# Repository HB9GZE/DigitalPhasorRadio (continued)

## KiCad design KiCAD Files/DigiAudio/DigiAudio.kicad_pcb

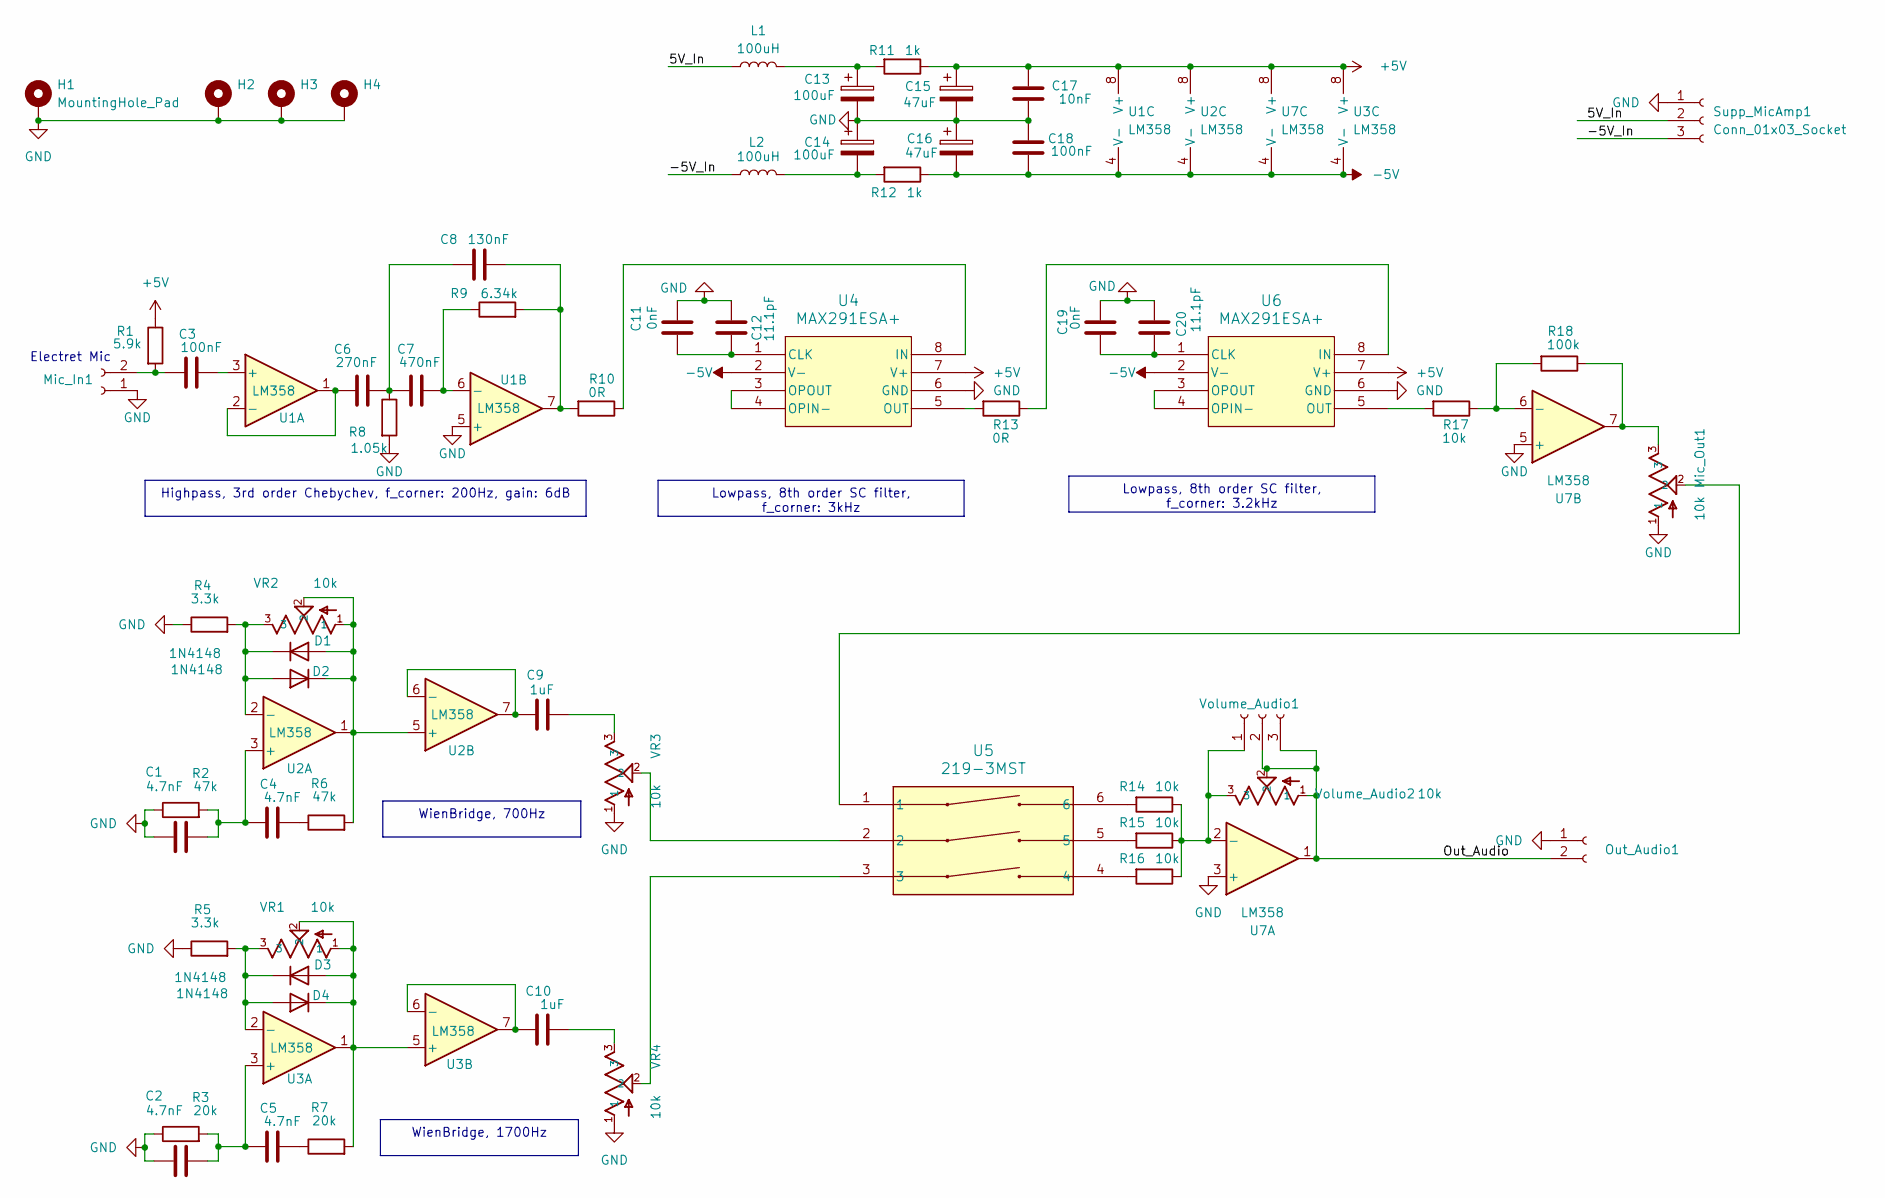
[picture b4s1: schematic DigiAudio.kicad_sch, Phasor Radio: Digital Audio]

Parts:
C1, C2, C4, C5: 4.7nF; C_0805_2012Metric_Pad1.18x1.45mm_HandSolder
C3, C18: 100nF; C_0805_2012Metric_Pad1.18x1.45mm_HandSolder
C6: 270nF; C_0805_2012Metric_Pad1.18x1.45mm_HandSolder
C7: 470nF; C_0805_2012Metric_Pad1.18x1.45mm_HandSolder
C8: 130nF; C_0805_2012Metric_Pad1.18x1.45mm_HandSolder
C9, C10: 1uF; C_0805_2012Metric_Pad1.18x1.45mm_HandSolder
C11, C19: 0nF; C_0805_2012Metric_Pad1.18x1.45mm_HandSolder
C12, C20: 11.1pF; C_0805_2012Metric_Pad1.18x1.45mm_HandSolder
C13, C14: 100uF; CP_EIA-3216-12_Kemet-S_Pad1.58x1.35mm_HandSolder
C15, C16: 47uF; CP_EIA-3216-12_Kemet-S_Pad1.58x1.35mm_HandSolder
C17: 10nF; C_0805_2012Metric_Pad1.18x1.45mm_HandSolder
D1, D2, D3, D4: 1N4148; D_SOD-123
H1, H2, H3, H4: MountingHole_Pad; MountingHole_2.5mm_Pad_TopBottom
L1, L2: 100uH; L_0805_2012Metric_Pad1.15x1.40mm_HandSolder
Mic_In1: Conn_01x02_Socket; JST_EH_B2B-EH-A_1x02_P2.50mm_Vertical
Mic_Out1: 10k; TRIM_35WR10KLFTR
Out_Audio1: Conn_01x02_Socket; JST_EH_B2B-EH-A_1x02_P2.50mm_Vertical
R1: 5.9k; R_0805_2012Metric_Pad1.20x1.40mm_HandSolder
R2, R6: 47k; R_0805_2012Metric_Pad1.20x1.40mm_HandSolder
R3, R7: 20k; R_0805_2012Metric_Pad1.20x1.40mm_HandSolder
R4, R5: 3.3k; R_0805_2012Metric_Pad1.20x1.40mm_HandSolder
R8: 1.05k; R_0805_2012Metric_Pad1.20x1.40mm_HandSolder
R9: 6.34k; R_0805_2012Metric_Pad1.20x1.40mm_HandSolder
R10, R13: 0R; R_0805_2012Metric_Pad1.20x1.40mm_HandSolder
R11, R12: 1k; R_0805_2012Metric_Pad1.20x1.40mm_HandSolder
R14, R15, R16, R17: 10k; R_0805_2012Metric_Pad1.20x1.40mm_HandSolder
R18: 100k; R_0805_2012Metric_Pad1.20x1.40mm_HandSolder
Supp_MicAmp1: Conn_01x03_Socket; JST_EH_B3B-EH-A_1x03_P2.50mm_Vertical
U1, U2, U3, U7: LM358; SOIC-8_3.9x4.9mm_P1.27mm
U4, U6: MAX291ESA+; MAX291
U5: 219-3MST; SW3_219-3MST_CTS
VR1, VR2, VR3, VR4: 10k; TRIM_35WR10KLFTR
Volume_Audio1: Conn_01x03_Socket; JST_EH_B3B-EH-A_1x03_P2.50mm_Vertical
Volume_Audio2: 10k; TRIM_35WR10KLFTR

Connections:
+5V: C15.1, C17.2, R1.1, R11.1, U1.8 (V+), U2.8 (V+), U3.8 (V+), U4.7 (V+), U6.7 (V+), U7.8 (V+)
-5V: C16.2, C18.1, R12.1, U1.4 (V-), U2.4 (V-), U3.4 (V-), U4.2 (V-), U6.2 (V-), U7.4 (V-)
/5V_In: L1.1, Supp_MicAmp1.2
/-5V_In: L2.1, Supp_MicAmp1.3
/Out_Audio: Out_Audio1.2, U7.1, Volume_Audio1.2, Volume_Audio1.3, Volume_Audio2.1, Volume_Audio2.2; also elsewhere on the board
GND: C1.1, C2.1, C11.2, C12.2, C13.2, C14.1, C15.2, C16.1, C17.1, C18.2, C19.2, C20.2, H1.1, H2.1, H3.1, H4.1, Mic_In1.1, Mic_Out1.1, Out_Audio1.1, R2.1, R3.1, R4.1, R5.1, R8.2, Supp_MicAmp1.1, U1.5 (+), U4.6 (GND), U6.6 (GND), U7.3 (+), U7.5 (+), VR3.1, VR4.1; also elsewhere on the board
unnamed: C4.2, R6.1
unnamed: C5.2, R7.1
unnamed: C6.2, C7.1, C8.1, R8.1
unnamed: C8.2, R9.2, R10.2, U1.7
unnamed: C9.2, VR3.3
unnamed: C10.2, VR4.3
unnamed: C13.1, L1.2, R11.2
unnamed: C14.2, L2.2, R12.2
unnamed: D1.2 (A), D2.1 (K), R6.2, U2.1, U2.5 (+), VR2.1, VR2.2
unnamed: D1.1 (K), D2.2 (A), R4.2, U2.2 (-), VR2.3
unnamed: D3.2 (A), D4.1 (K), R7.2, U3.1, U3.5 (+), VR1.1, VR1.2
unnamed: D3.1 (K), D4.2 (A), R5.2, U3.2 (-), VR1.3
unnamed 18: C3.1, Mic_In1.2, R1.2; also elsewhere on the board
unnamed 19: Mic_Out1.2, U5.1; also elsewhere on the board
unnamed 20: Mic_Out1.3, R18.1, U7.7; also elsewhere on the board
unnamed: R14.2, U5.6
unnamed: R15.2, U5.5
unnamed: R16.2, U5.4
unnamed: C3.2, U1.3 (+)
unnamed: C6.1, U1.1, U1.2 (-)
unnamed: C7.2, R9.1, U1.6 (-)
unnamed: C1.2, C4.1, R2.2, U2.3 (+)
unnamed: C9.1, U2.6 (-), U2.7
unnamed: C2.2, C5.1, R3.2, U3.3 (+)
unnamed: C10.1, U3.6 (-), U3.7
unnamed: C11.1, C12.1, U4.1 (CLK)
unnamed: R10.1, U4.8 (IN)
unnamed: U4.3 (OPOUT), U4.4 (OPIN-)
unnamed: R13.2, U4.5 (OUT)
unnamed: U5.2, VR3.2
unnamed: U5.3, VR4.2
unnamed: C19.1, C20.1, U6.1 (CLK)
unnamed: R13.1, U6.8 (IN)
unnamed: U6.3 (OPOUT), U6.4 (OPIN-)
unnamed: R17.2, U6.5 (OUT)
unnamed 41: R14.1, R15.1, R16.1, U7.2 (-), Volume_Audio1.1, Volume_Audio2.3; also elsewhere on the board
unnamed: R17.1, R18.2, U7.6 (-)

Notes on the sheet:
Lowpass, 8th order SC filter, f_corner: 3kHz
WienBridge, 1700Hz
Highpass, 3rd order Chebychev, f_corner: 200Hz, gain: 6dB
WienBridge, 700Hz
Lowpass, 8th order SC filter, f_corner: 3.2kHz
Electret Mic

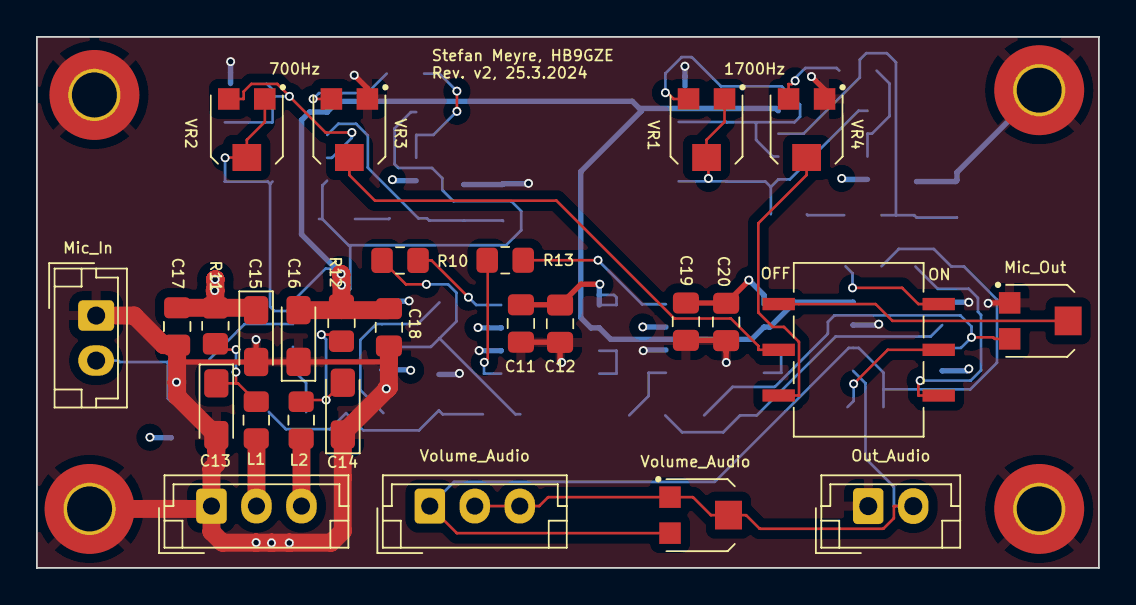
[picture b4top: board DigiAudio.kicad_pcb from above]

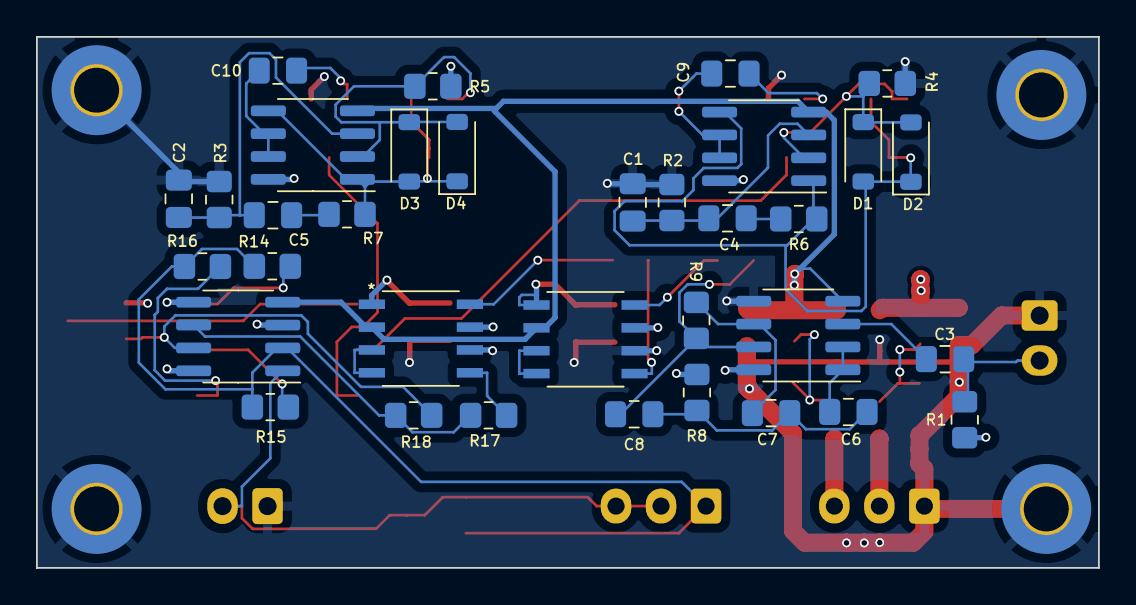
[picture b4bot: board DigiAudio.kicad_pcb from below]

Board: 4 copper layers, 59.0 x 29.5 mm, 65 parts (34 on the bottom side), 43 nets.

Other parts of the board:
Mic_In: Conn_01x02_Socket; JST_EH_B2B-EH-A_1x02_P2.50mm_Vertical
Mic_Out: 10k; TRIM_35WR10KLFTR
Out_Audio: Conn_01x02_Socket; JST_EH_B2B-EH-A_1x02_P2.50mm_Vertical
Volume_Audio: 10k; TRIM_35WR10KLFTR
Volume_Audio#2: Conn_01x03_Socket; JST_EH_B3B-EH-A_1x03_P2.50mm_Vertical

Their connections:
/Out_Audio: Out_Audio.2, Volume_Audio.1, Volume_Audio.2, Volume_Audio#2.2, Volume_Audio#2.3; also elsewhere on the board
GND: Mic_In.1, Mic_Out.1, Out_Audio.1; also elsewhere on the board
unnamed 18: Mic_In.2; also elsewhere on the board
unnamed 19: Mic_Out.2; also elsewhere on the board
unnamed 20: Mic_Out.3; also elsewhere on the board
unnamed 41: Volume_Audio.3, Volume_Audio#2.1; also elsewhere on the board

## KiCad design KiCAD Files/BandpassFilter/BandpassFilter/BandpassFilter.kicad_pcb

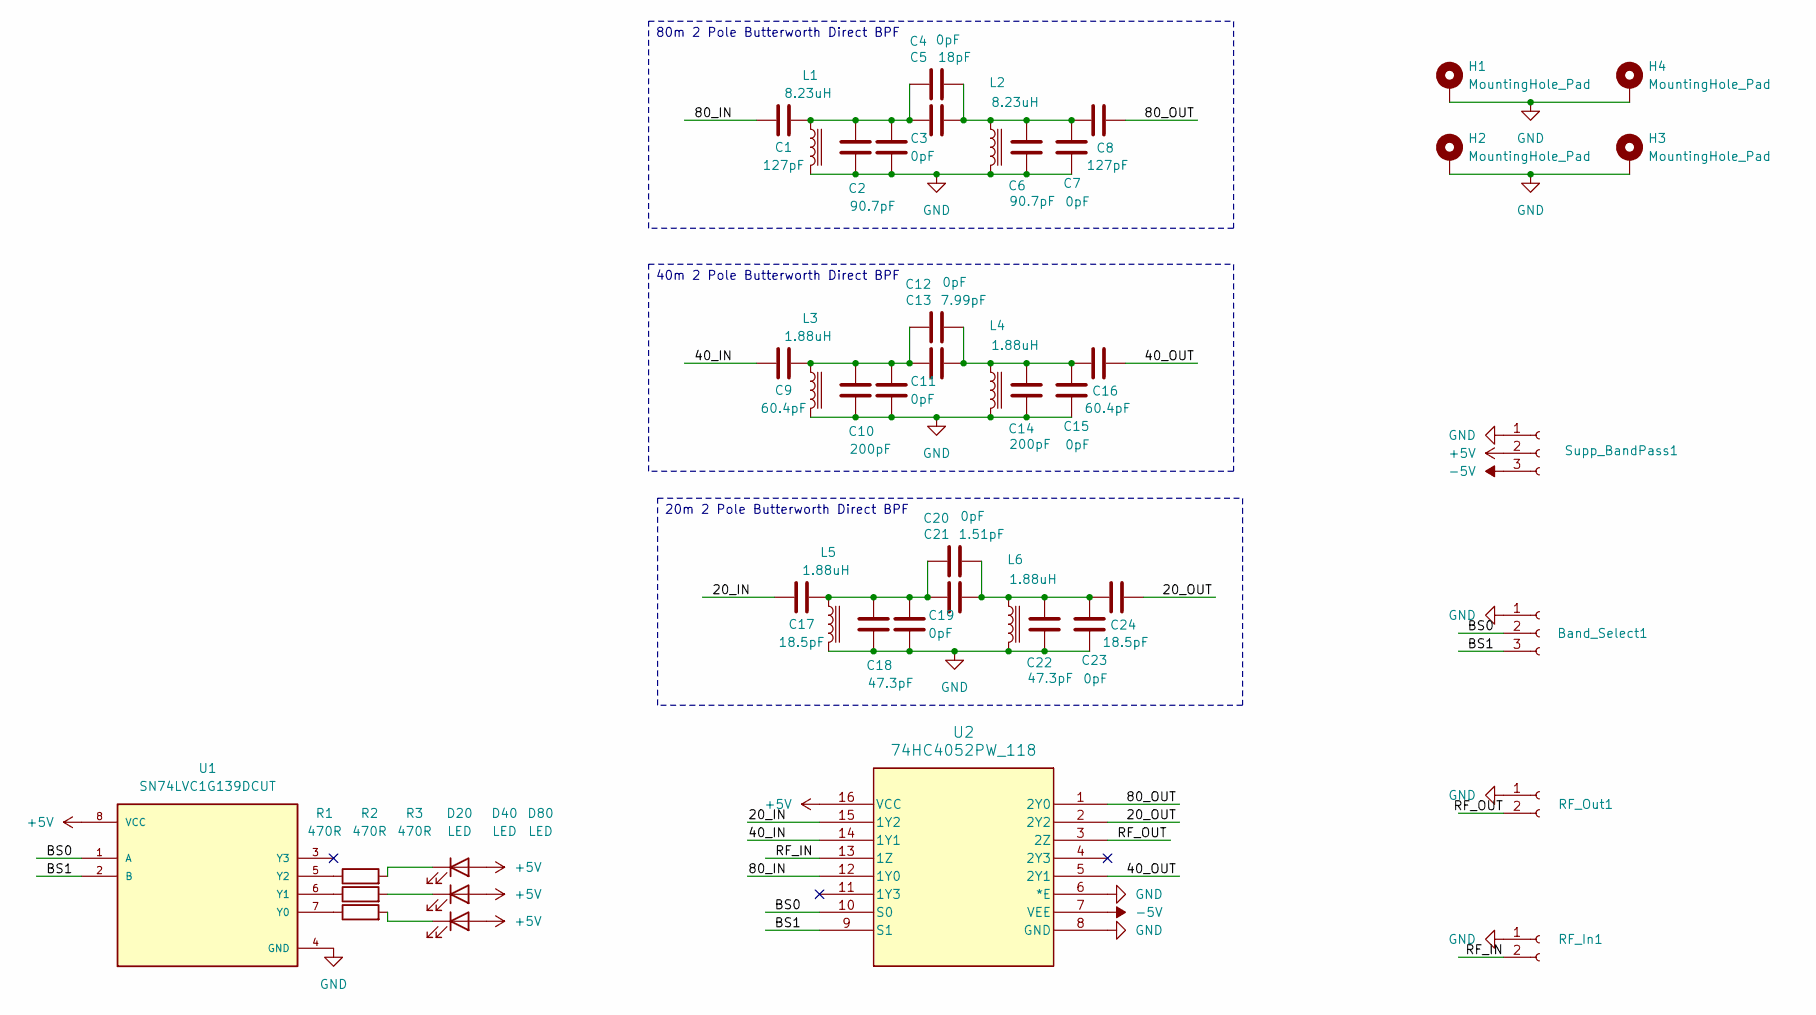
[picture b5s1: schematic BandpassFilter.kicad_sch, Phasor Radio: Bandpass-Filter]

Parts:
Band_Select1: JST_EH_B3B-EH-A_1x03_P2.50mm_Vertical
C1, C8: 127pF; C_0805_2012Metric_Pad1.18x1.45mm_HandSolder
C2, C6: 90.7pF; C_0805_2012Metric_Pad1.18x1.45mm_HandSolder
C3, C4, C7, C11, C12, C15, C19, C20, C23: 0pF; C_0805_2012Metric_Pad1.18x1.45mm_HandSolder
C5: 18pF; C_0805_2012Metric_Pad1.18x1.45mm_HandSolder
C9, C16: 60.4pF; C_0805_2012Metric_Pad1.18x1.45mm_HandSolder
C10, C14: 200pF; C_0805_2012Metric_Pad1.18x1.45mm_HandSolder
C13: 7.99pF; C_0805_2012Metric_Pad1.18x1.45mm_HandSolder
C17, C24: 18.5pF; C_0805_2012Metric_Pad1.18x1.45mm_HandSolder
C18, C22: 47.3pF; C_0805_2012Metric_Pad1.18x1.45mm_HandSolder
C21: 1.51pF; C_0805_2012Metric_Pad1.18x1.45mm_HandSolder
D20, D40, D80: LED; LED_0805_2012Metric_Pad1.15x1.40mm_HandSolder
H1, H2, H3, H4: MountingHole_Pad; MountingHole_2.5mm_Pad_TopBottom
L1, L2: 8.23uH; L_Toroid_Vertical_L19.1mm_W8.1mm_P7.10mm_Bourns_5700
L3, L4, L5, L6: 1.88uH; L_Toroid_Vertical_L19.1mm_W8.1mm_P7.10mm_Bourns_5700
R1, R2, R3: 470R; R_0805_2012Metric_Pad1.20x1.40mm_HandSolder
RF_In1: PinHeader_1x02_P2.54mm_Vertical
RF_Out1: PinHeader_1x02_P2.54mm_Vertical
Supp_BandPass1: JST_EH_B3B-EH-A_1x03_P2.50mm_Vertical
U1: SN74LVC1G139DCUT; SOP50P310X90-8N; PARTREV E
U2: 74HC4052PW_118; TSSOP16_5P1X4P5_NEX

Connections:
+5V: D20.2 (A), D40.2 (A), D80.2 (A), Supp_BandPass1.2, U1.8 (VCC), U2.16 (VCC); also elsewhere on the board
-5V: Supp_BandPass1.3, U2.7 (VEE); also elsewhere on the board
/20_IN: C17.1, U2.15 (1Y2)
/20_OUT: C24.2, U2.2 (2Y2)
/40_IN: C9.1, U2.14 (1Y1)
/40_OUT: C16.2, U2.5 (2Y1)
/80_IN: C1.1, U2.12 (1Y0)
/80_OUT: C8.2, U2.1 (2Y0)
/BS0: Band_Select1.2, U1.1 (A), U2.10 (S0); also elsewhere on the board
/BS1: Band_Select1.3, U1.2 (B), U2.9 (S1); also elsewhere on the board
/RF_IN: RF_In1.2, U2.13 (1Z); also elsewhere on the board
/RF_OUT: RF_Out1.2, U2.3 (2Z); also elsewhere on the board
GND: Band_Select1.1, C2.1, C3.1, C6.1, C7.1, C10.1, C11.1, C14.1, C15.1, C18.1, C19.1, C22.1, C23.1, H1.1, H2.1, H3.1, H4.1, L1.2, L2.2, L3.2, L4.2, L5.2, L6.2, RF_In1.1, RF_Out1.1, Supp_BandPass1.1, U1.4 (GND), U2.6 (*E), U2.8 (GND); also elsewhere on the board
unnamed: C1.2, C2.2, C3.2, C4.2, C5.2, L1.1
unnamed: C4.1, C5.1, C6.2, C7.2, C8.1, L2.1
unnamed: C9.2, C10.2, C11.2, C12.2, C13.2, L3.1
unnamed: C12.1, C13.1, C14.2, C15.2, C16.1, L4.1
unnamed: C17.2, C18.2, C19.2, C20.2, C21.2, L5.1
unnamed: C20.1, C21.1, C22.2, C23.2, C24.1, L6.1
unnamed: D20.1 (K), R1.2
unnamed: D40.1 (K), R2.2
unnamed: D80.1 (K), R3.2
unnamed: R3.1, U1.7 (Y0)
unnamed: R2.1, U1.6 (Y1)
unnamed: R1.1, U1.5 (Y2)

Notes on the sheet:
40m 2 Pole Butterworth Direct BPF
20m 2 Pole Butterworth Direct BPF
80m 2 Pole Butterworth Direct BPF

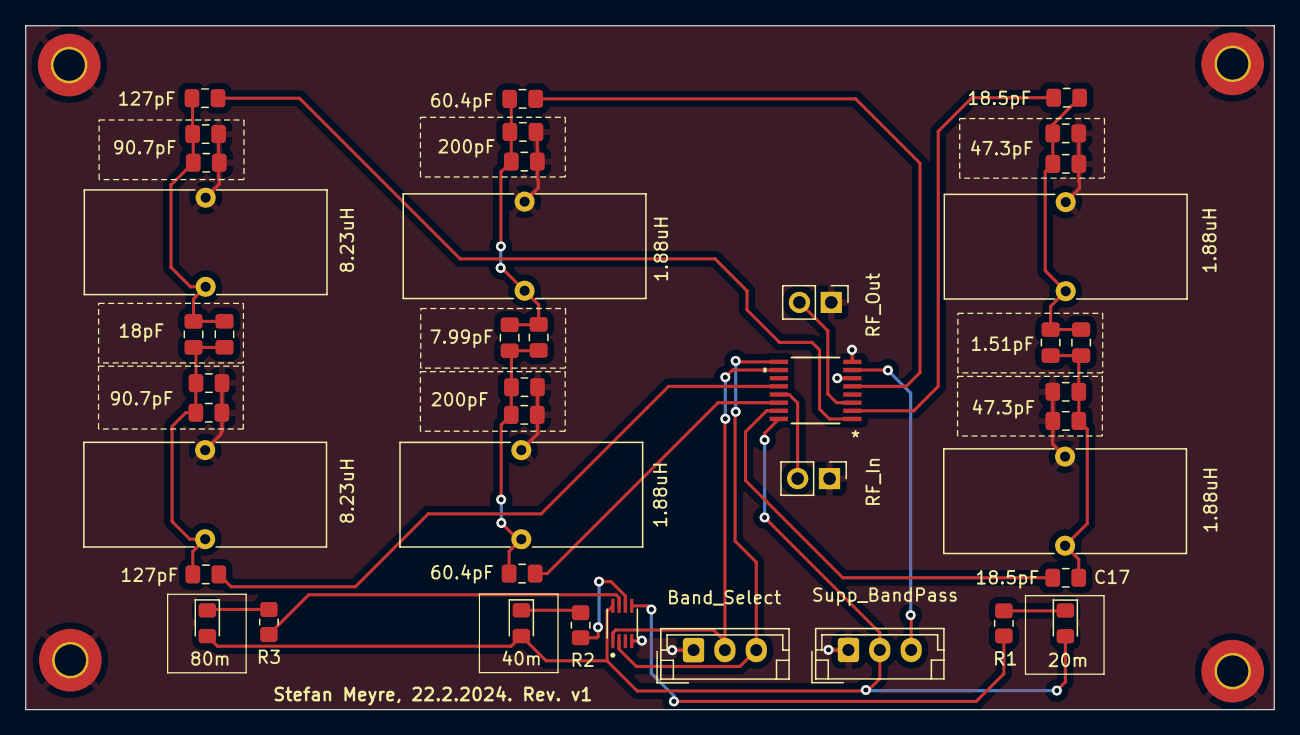
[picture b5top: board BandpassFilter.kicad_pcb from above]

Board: 2 copper layers, 99.5 x 54.5 mm, 46 parts (0 on the bottom side), 25 nets.

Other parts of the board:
Band_Select: JST_EH_B3B-EH-A_1x03_P2.50mm_Vertical
RF_In: PinHeader_1x02_P2.54mm_Vertical
RF_Out: PinHeader_1x02_P2.54mm_Vertical
Supp_BandPass: JST_EH_B3B-EH-A_1x03_P2.50mm_Vertical

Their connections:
+5V: Supp_BandPass.2; also elsewhere on the board
-5V: Supp_BandPass.3; also elsewhere on the board
/BS0: Band_Select.2; also elsewhere on the board
/BS1: Band_Select.3; also elsewhere on the board
/RF_IN: RF_In.2; also elsewhere on the board
/RF_OUT: RF_Out.2; also elsewhere on the board
GND: Band_Select.1, RF_In.1, RF_Out.1, Supp_BandPass.1; also elsewhere on the board

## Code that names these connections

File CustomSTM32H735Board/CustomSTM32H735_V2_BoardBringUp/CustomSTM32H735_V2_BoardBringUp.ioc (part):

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Mcu.Name=STM32H735IGKx
Mcu.Package=UFBGA176
Mcu.UserName=STM32H735IGKx
PA0.GPIOParameters=GPIO_Speed,GPIO_Label
PA0.GPIO_Label=VSYNC_FREQ
PA0.GPIO_Speed=GPIO_SPEED_FREQ_VERY_HIGH
PA0.Signal=GPIO_Output
PA0_C.Signal=ADCx_INP0
PA12.GPIOParameters=GPIO_Label
PA12.GPIO_Label=LSBUSB
PA12.Signal=GPIO_Output
PA13(JTMS/SWDIO).Mode=Serial_Wire
PA13(JTMS/SWDIO).Signal=DEBUG_JTMS-SWDIO
PA14(JTCK/SWCLK).Mode=Serial_Wire
PA14(JTCK/SWCLK).Signal=DEBUG_JTCK-SWCLK
PA15(JTDI).Signal=S_TIM2_CH1_ETR
PA1_C.Signal=ADCx_INP1
PA3.GPIOParameters=GPIO_Speed
PA3.GPIO_Speed=GPIO_SPEED_FREQ_VERY_HIGH
PA3.Mode=RGB888
PA3.Signal=LTDC_B5
PA4.GPIOParameters=GPIO_Speed
PA4.GPIO_Speed=GPIO_SPEED_FREQ_VERY_HIGH
PA4.Mode=RGB888
PA4.Signal=LTDC_VSYNC
PA5.Signal=COMP_DAC12_group
PA6.GPIOParameters=GPIO_Speed
PA6.GPIO_Speed=GPIO_SPEED_FREQ_VERY_HIGH
PA6.Mode=RGB888
PA6.Signal=LTDC_G2
PA8.GPIOParameters=GPIO_Speed
PA8.GPIO_Speed=GPIO_SPEED_FREQ_VERY_HIGH
PA8.Mode=RGB888
PA8.Signal=LTDC_B3
PB0.GPIOParameters=GPIO_Speed
PB0.GPIO_Speed=GPIO_SPEED_FREQ_VERY_HIGH
PB0.Mode=RGB888
PB0.Signal=LTDC_G1
PB1.GPIOParameters=GPIO_Speed
PB1.GPIO_Speed=GPIO_SPEED_FREQ_VERY_HIGH
PB1.Mode=RGB888
PB1.Signal=LTDC_G0
PB10.Mode=I2C
PB10.Signal=I2C2_SCL
PB11.Mode=I2C
PB11.Signal=I2C2_SDA
PB12.GPIOParameters=GPIO_Label
PB12.GPIO_Label=S0
PB12.Signal=GPIO_Output
PB13.GPIOParameters=GPIO_Label
PB13.GPIO_Label=S1
PB13.Signal=GPIO_Output
PB14.GPIOParameters=GPIO_Speed,GPIO_Label
PB14.GPIO_Label=FRAME_RATE
PB14.GPIO_Speed=GPIO_SPEED_FREQ_VERY_HIGH
PB14.Signal=GPIO_Output
PB15.GPIOParameters=GPIO_Speed,GPIO_Label
PB15.GPIO_Label=MCU_ACTIVE
PB15.GPIO_Speed=GPIO_SPEED_FREQ_VERY_HIGH
PB15.Signal=GPIO_Output
PB2.Mode=OCTOSPI1_Port1_DQS
PB2.Signal=OCTOSPIM_P1_DQS
PB3(JTDO/TRACESWO).Signal=S_TIM2_CH2
PB8.GPIOParameters=GPIO_Speed
PB8.GPIO_Speed=GPIO_SPEED_FREQ_VERY_HIGH
PB8.Mode=RGB888
PB8.Signal=LTDC_B6
PB9.GPIOParameters=GPIO_Speed
PB9.GPIO_Speed=GPIO_SPEED_FREQ_VERY_HIGH
PB9.Mode=RGB888
PB9.Signal=LTDC_B7
PC13.GPIOParameters=GPIO_Label
PC13.GPIO_Label=GPIO_PC13
PC13.Signal=GPIO_Output
PC2_C.Mode=IN0-Single-Ended
PC2_C.Signal=ADC3_INP0
PC4.Mode=Follower-DAC_OUT1-INP
PC4.Signal=OPAMP1_VOUT
PC6.GPIOParameters=GPIO_Speed
PC6.GPIO_Speed=GPIO_SPEED_FREQ_VERY_HIGH
PC6.Mode=RGB888
PC6.Signal=LTDC_HSYNC
PC7.GPIOParameters=GPIO_Speed
PC7.GPIO_Speed=GPIO_SPEED_FREQ_VERY_HIGH
PC7.Mode=RGB888
PC7.Signal=LTDC_G6
PC9.Mode=I2C
PC9.Signal=I2C3_SDA
PD0.GPIOParameters=GPIO_Speed
PD0.GPIO_Speed=GPIO_SPEED_FREQ_VERY_HIGH
PD0.Mode=RGB888
PD0.Signal=LTDC_B1
PD1.Mode=Asynchronous
PD1.Signal=UART4_TX
PD10.GPIOParameters=GPIO_Speed,PinState,GPIO_PuPd,GPIO_Label
PD10.GPIO_Label=LCD_DISP
PD10.GPIO_PuPd=GPIO_NOPULL
PD10.GPIO_Speed=GPIO_SPEED_FREQ_LOW
PD10.PinState=GPIO_PIN_RESET
PD10.Signal=GPIO_Output
PD11.Mode=OCTOSPI1_IOL_Port1L
PD11.Signal=OCTOSPIM_P1_IO0
PD12.Mode=OCTOSPI1_IOL_Port1L
PD12.Signal=OCTOSPIM_P1_IO1
PD13.Mode=OCTOSPI1_IOL_Port1L
PD13.Signal=OCTOSPIM_P1_IO3
PD3.GPIOParameters=GPIO_Speed
PD3.GPIO_Speed=GPIO_SPEED_FREQ_VERY_HIGH
PD3.Mode=RGB888
PD3.Signal=LTDC_G7
PD4.Mode=OCTOSPI1_IOH_Port1H
PD4.Signal=OCTOSPIM_P1_IO4
PD5.Mode=OCTOSPI1_IOH_Port1H
PD5.Signal=OCTOSPIM_P1_IO5
PD6.GPIOParameters=GPIO_Speed
PD6.GPIO_Speed=GPIO_SPEED_FREQ_VERY_HIGH
PD6.Mode=RGB888
PD6.Signal=LTDC_B2
PD7.Mode=OCTOSPI1_IOH_Port1H
PD7.Signal=OCTOSPIM_P1_IO7
PE0.GPIOParameters=GPIO_Speed
PE0.GPIO_Speed=GPIO_SPEED_FREQ_VERY_HIGH
PE0.Mode=RGB888
PE0.Signal=LTDC_R0
PE1.GPIOParameters=GPIO_Speed
PE1.GPIO_Speed=GPIO_SPEED_FREQ_VERY_HIGH
PE1.Mode=RGB888
PE1.Signal=LTDC_R6
PE11.GPIOParameters=GPIO_Speed
PE11.GPIO_Speed=GPIO_SPEED_FREQ_VERY_HIGH
PE11.Mode=RGB888
PE11.Signal=LTDC_G3
PE12.GPIOParameters=GPIO_Speed
PE12.GPIO_Speed=GPIO_SPEED_FREQ_VERY_HIGH
PE12.Mode=RGB888
PE12.Signal=LTDC_B4
PE13.GPIOParameters=GPIO_Speed
PE13.GPIO_Speed=GPIO_SPEED_FREQ_VERY_HIGH
PE13.Mode=RGB888
PE13.Signal=LTDC_DE
PE15.GPIOParameters=GPIO_Speed
PE15.GPIO_Speed=GPIO_SPEED_FREQ_VERY_HIGH
PE15.Mode=RGB888
PE15.Signal=LTDC_R7
PE2.Mode=OCTOSPI1_IOL_Port1L
PE2.Signal=OCTOSPIM_P1_IO2
PE4.GPIOParameters=GPIO_Label
PE4.GPIO_Label=GPIO_PE4
PE4.Signal=GPIO_Output
PF0.Mode=OCTOSPI2_IOL_Port2L
PF0.Signal=OCTOSPIM_P2_IO0
PF1.Mode=OCTOSPI2_IOL_Port2L
PF1.Signal=OCTOSPIM_P2_IO1
PF10.Mode=O1_P1_CLK
PF10.Signal=OCTOSPIM_P1_CLK
PF12.Mode=OCTOSPI2_Port2_DQS
PF12.Signal=OCTOSPIM_P2_DQS
PF14.Mode=I2C
PF14.Signal=I2C4_SCL
PF15.Mode=I2C
PF15.Signal=I2C4_SDA
PF2.Mode=OCTOSPI2_IOL_Port2L
PF2.Signal=OCTOSPIM_P2_IO2
PF3.Mode=OCTOSPI2_IOL_Port2L
PF3.Signal=OCTOSPIM_P2_IO3
PF4.Mode=O2_P2_CLK
PF4.Signal=OCTOSPIM_P2_CLK
PF6.Mode=Encoder_Interface
PF6.Signal=TIM23_CH1
PG0.Mode=OCTOSPI2_IOH_Port2H
PG0.Signal=OCTOSPIM_P2_IO4
PG1.Mode=OCTOSPI2_IOH_Port2H
PG1.Signal=OCTOSPIM_P2_IO5
PG10.Mode=OCTOSPI2_IOH_Port2H
PG10.Signal=OCTOSPIM_P2_IO6
PG11.Mode=OCTOSPI2_IOH_Port2H
PG11.Signal=OCTOSPIM_P2_IO7
PG12.Mode=OCTOSPI2_Port2_NCS
PG12.Signal=OCTOSPIM_P2_NCS
PG13.Signal=S_TIM23_CH2
PG14.GPIOParameters=GPIO_Speed
PG14.GPIO_Speed=GPIO_SPEED_FREQ_VERY_HIGH
PG14.Mode=RGB888
PG14.Signal=LTDC_B0
PG15.GPIOParameters=GPIO_Label
PG15.GPIO_Label=LCD_BL_CTRL
PG15.Signal=GPIO_Output
PG2.GPIOParameters=GPIO_Label
PG2.GPIO_Label=CTP_INT
PG2.Signal=GPXTI2
PG3.GPIOParameters=GPIO_Speed,GPIO_Label
PG3.GPIO_Label=RENDER_TIME
PG3.GPIO_Speed=GPIO_SPEED_FREQ_VERY_HIGH
PG3.Signal=GPIO_Output
PG5.GPIOParameters=GPIO_Label
PG5.GPIO_Label=RXTX
PG5.Signal=GPIO_Output
PG6.Mode=OCTOSPI1_Port1_NCS
PG6.Signal=OCTOSPIM_P1_NCS
PG7.GPIOParameters=GPIO_Speed
PG7.GPIO_Speed=GPIO_SPEED_FREQ_VERY_HIGH
PG7.Mode=RGB888
PG7.Signal=LTDC_CLK
PG9.Mode=OCTOSPI1_IOH_Port1H
PG9.Signal=OCTOSPIM_P1_IO6
PH0-OSC_IN.Mode=HSE-External-Oscillator
PH0-OSC_IN.Signal=RCC_OSC_IN
PH1-OSC_OUT.Mode=HSE-External-Oscillator
PH1-OSC_OUT.Signal=RCC_OSC_OUT
PH10.GPIOParameters=GPIO_Speed
PH10.GPIO_Speed=GPIO_SPEED_FREQ_VERY_HIGH
PH10.Mode=RGB888
PH10.Signal=LTDC_R4
PH11.GPIOParameters=GPIO_Speed
PH11.GPIO_Speed=GPIO_SPEED_FREQ_VERY_HIGH
PH11.Mode=RGB888
PH11.Signal=LTDC_R5
PH12.GPIOParameters=GPIO_Label
PH12.GPIO_Label=NRXTX
PH12.Signal=GPIO_Output
PH14.Mode=Asynchronous
PH14.Signal=UART4_RX
PH15.GPIOParameters=GPIO_Speed
PH15.GPIO_Speed=GPIO_SPEED_FREQ_VERY_HIGH
PH15.Mode=RGB888
PH15.Signal=LTDC_G4
PH3.GPIOParameters=GPIO_Speed
PH3.GPIO_Speed=GPIO_SPEED_FREQ_VERY_HIGH
PH3.Mode=RGB888
PH3.Signal=LTDC_R1
PH4.GPIOParameters=GPIO_Speed
PH4.GPIO_Speed=GPIO_SPEED_FREQ_VERY_HIGH
PH4.Mode=RGB888
PH4.Signal=LTDC_G5
PH6.GPIOParameters=GPIO_Label
PH6.GPIO_Label=LCD_RST
PH6.Signal=GPIO_Output
PH7.Mode=I2C
PH7.Signal=I2C3_SCL
PH8.GPIOParameters=GPIO_Speed
PH8.GPIO_Speed=GPIO_SPEED_FREQ_VERY_HIGH
PH8.Mode=RGB888
PH8.Signal=LTDC_R2
PH9.GPIOParameters=GPIO_Speed
PH9.GPIO_Speed=GPIO_SPEED_FREQ_VERY_HIGH
PH9.Mode=RGB888
PH9.Signal=LTDC_R3
RCC.SYSCLKFreq_VALUE=275000000
RCC.SYSCLKSource=RCC_SYSCLKSOURCE_PLLCLK
board=custom

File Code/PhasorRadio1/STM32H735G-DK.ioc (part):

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Mcu.Name=STM32H735IGKx
Mcu.Package=UFBGA176
Mcu.UserName=STM32H735IGKx
PA0.GPIOParameters=GPIO_Speed,GPIO_Label
PA0.GPIO_Label=VSYNC_FREQ
PA0.GPIO_Speed=GPIO_SPEED_FREQ_VERY_HIGH
PA0.Signal=GPIO_Output
PA0_C.Signal=ADCx_INP0
PA12.Signal=GPIO_Output
PA1_C.Signal=ADCx_INP1
PA3.GPIOParameters=GPIO_Speed
PA3.GPIO_Speed=GPIO_SPEED_FREQ_VERY_HIGH
PA3.Mode=RGB888
PA3.Signal=LTDC_B5
PA4.GPIOParameters=GPIO_Speed
PA4.GPIO_Speed=GPIO_SPEED_FREQ_VERY_HIGH
PA4.Mode=RGB888
PA4.Signal=LTDC_VSYNC
PA5.Signal=COMP_DAC12_group
PA6.GPIOParameters=GPIO_Speed
PA6.GPIO_Speed=GPIO_SPEED_FREQ_VERY_HIGH
PA6.Mode=RGB888
PA6.Signal=LTDC_G2
PA8.GPIOParameters=GPIO_Speed
PA8.GPIO_Speed=GPIO_SPEED_FREQ_VERY_HIGH
PA8.Mode=RGB888
PA8.Signal=LTDC_B3
PB0.GPIOParameters=GPIO_Speed
PB0.GPIO_Speed=GPIO_SPEED_FREQ_VERY_HIGH
PB0.Mode=RGB888
PB0.Signal=LTDC_G1
PB1.GPIOParameters=GPIO_Speed
PB1.GPIO_Speed=GPIO_SPEED_FREQ_VERY_HIGH
PB1.Mode=RGB888
PB1.Signal=LTDC_G0
PB12.Signal=GPIO_Output
PB13.Signal=GPIO_Output
PB14.GPIOParameters=GPIO_Speed,GPIO_PuPd,GPIO_Label,GPIO_ModeDefaultOutputPP
PB14.GPIO_Label=FRAME_RATE
PB14.GPIO_ModeDefaultOutputPP=GPIO_MODE_OUTPUT_PP
PB14.GPIO_PuPd=GPIO_NOPULL
PB14.GPIO_Speed=GPIO_SPEED_FREQ_VERY_HIGH
PB14.Signal=GPIO_Output
PB15.GPIOParameters=GPIO_Speed,GPIO_Label
PB15.GPIO_Label=MCU_ACTIVE
PB15.GPIO_Speed=GPIO_SPEED_FREQ_VERY_HIGH
PB15.Signal=GPIO_Output
PB2.Mode=OCTOSPI1_Port1_DQS
PB2.Signal=OCTOSPIM_P1_DQS
PB8.Mode=RGB888
PB8.Signal=LTDC_B6
PB9.GPIOParameters=GPIO_Speed
PB9.GPIO_Speed=GPIO_SPEED_FREQ_VERY_HIGH
PB9.Mode=RGB888
PB9.Signal=LTDC_B7
PC2_C.Mode=IN0-Single-Ended
PC2_C.Signal=ADC3_INP0
PC4.Mode=Follower-DAC_OUT1-INP
PC4.Signal=OPAMP1_VOUT
PC6.Mode=RGB888
PC6.Signal=LTDC_HSYNC
PC7.Mode=RGB888
PC7.Signal=LTDC_G6
PC9.Mode=I2C
PC9.Signal=I2C3_SDA
PD0.Mode=RGB888
PD0.Signal=LTDC_B1
PD1.Mode=Asynchronous
PD1.Signal=UART4_TX
PD10.GPIOParameters=GPIO_Speed,PinState,GPIO_PuPd,GPIO_Label
PD10.GPIO_Label=LCD_DISP
PD10.GPIO_PuPd=GPIO_NOPULL
PD10.GPIO_Speed=GPIO_SPEED_FREQ_LOW
PD10.PinState=GPIO_PIN_RESET
PD10.Signal=GPIO_Output
PD11.Mode=OCTOSPI1_IOL_Port1L
PD11.Signal=OCTOSPIM_P1_IO0
PD12.Mode=OCTOSPI1_IOL_Port1L
PD12.Signal=OCTOSPIM_P1_IO1
PD13.Mode=OCTOSPI1_IOL_Port1L
PD13.Signal=OCTOSPIM_P1_IO3
PD15.Signal=GPIO_Output
PD3.Mode=RGB888
PD3.Signal=LTDC_G7
PD4.Mode=OCTOSPI1_IOH_Port1H
PD4.Signal=OCTOSPIM_P1_IO4
PD5.Mode=OCTOSPI1_IOH_Port1H
PD5.Signal=OCTOSPIM_P1_IO5
PD6.GPIOParameters=GPIO_Speed
PD6.GPIO_Speed=GPIO_SPEED_FREQ_VERY_HIGH
PD6.Mode=RGB888
PD6.Signal=LTDC_B2
PD7.Mode=OCTOSPI1_IOH_Port1H
PD7.Signal=OCTOSPIM_P1_IO7
PE1.GPIOParameters=GPIO_Speed
PE1.GPIO_Speed=GPIO_SPEED_FREQ_VERY_HIGH
PE1.Mode=RGB888
PE1.Signal=LTDC_R6
PE11.GPIOParameters=GPIO_Speed
PE11.GPIO_Speed=GPIO_SPEED_FREQ_VERY_HIGH
PE11.Mode=RGB888
PE11.Signal=LTDC_G3
PE12.GPIOParameters=GPIO_Speed
PE12.GPIO_Speed=GPIO_SPEED_FREQ_VERY_HIGH
PE12.Mode=RGB888
PE12.Signal=LTDC_B4
PE13.GPIOParameters=GPIO_Speed
PE13.GPIO_Speed=GPIO_SPEED_FREQ_VERY_HIGH
PE13.Mode=RGB888
PE13.Signal=LTDC_DE
PE14.Signal=GPIO_Output
PE15.GPIOParameters=GPIO_Speed
PE15.GPIO_Speed=GPIO_SPEED_FREQ_VERY_HIGH
PE15.Mode=RGB888
PE15.Signal=LTDC_R7
PE2.Mode=OCTOSPI1_IOL_Port1L
PE2.Signal=OCTOSPIM_P1_IO2
PE3.Signal=GPIO_Output
PF0.Mode=OCTOSPI2_IOL_Port2L
PF0.Signal=OCTOSPIM_P2_IO0
PF1.Mode=OCTOSPI2_IOL_Port2L
PF1.Signal=OCTOSPIM_P2_IO1
PF10.Mode=O1_P1_CLK
PF10.Signal=OCTOSPIM_P1_CLK
PF12.Mode=OCTOSPI2_Port2_DQS
PF12.Signal=OCTOSPIM_P2_DQS
PF14.GPIOParameters=GPIO_Speed,GPIO_Pu
PF14.GPIO_Pu=GPIO_NOPULL
PF14.GPIO_Speed=GPIO_SPEED_FREQ_LOW
PF14.Mode=I2C
PF14.Signal=I2C4_SCL
PF15.GPIOParameters=GPIO_Speed,GPIO_Pu
PF15.GPIO_Pu=GPIO_NOPULL
PF15.GPIO_Speed=GPIO_SPEED_FREQ_LOW
PF15.Mode=I2C
PF15.Signal=I2C4_SDA
PF2.Mode=OCTOSPI2_IOL_Port2L
PF2.Signal=OCTOSPIM_P2_IO2
PF3.Mode=OCTOSPI2_IOL_Port2L
PF3.Signal=OCTOSPIM_P2_IO3
PF4.Mode=O2_P2_CLK
PF4.Signal=OCTOSPIM_P2_CLK
PF6.Mode=Encoder_Interface
PF6.Signal=TIM23_CH1
PG0.Mode=OCTOSPI2_IOH_Port2H
PG0.Signal=OCTOSPIM_P2_IO4
PG1.Mode=OCTOSPI2_IOH_Port2H
PG1.Signal=OCTOSPIM_P2_IO5
PG10.Mode=OCTOSPI2_IOH_Port2H
PG10.Signal=OCTOSPIM_P2_IO6
PG11.Mode=OCTOSPI2_IOH_Port2H
PG11.Signal=OCTOSPIM_P2_IO7
PG12.Mode=OCTOSPI2_Port2_NCS
PG12.Signal=OCTOSPIM_P2_NCS
PG13.GPIOParameters=GPIO_Speed
PG13.GPIO_Speed=GPIO_SPEED_FREQ_HIGH
PG13.Signal=S_TIM23_CH2
PG14.GPIOParameters=GPIO_Speed
PG14.GPIO_Speed=GPIO_SPEED_FREQ_VERY_HIGH
PG14.Mode=RGB888
PG14.Signal=LTDC_B0
PG15.GPIOParameters=GPIO_Label
PG15.GPIO_Label=LCD_BL_CTRL
PG15.Signal=GPIO_Output
PG3.GPIOParameters=GPIO_Speed,GPIO_Label
PG3.GPIO_Label=RENDER_TIME
PG3.GPIO_Speed=GPIO_SPEED_FREQ_VERY_HIGH
PG3.Signal=GPIO_Output
PG4.Signal=GPIO_Output
PG5.Signal=GPIO_Output
PG6.Mode=OCTOSPI1_Port1_NCS
PG6.Signal=OCTOSPIM_P1_NCS
PG7.Mode=RGB888
PG7.Signal=LTDC_CLK
PG9.Mode=OCTOSPI1_IOH_Port1H
PG9.Signal=OCTOSPIM_P1_IO6
PH0-OSC_IN.Mode=HSE-External-Oscillator
PH0-OSC_IN.Signal=RCC_OSC_IN
PH1-OSC_OUT.Mode=HSE-External-Oscillator
PH1-OSC_OUT.Signal=RCC_OSC_OUT
PH10.GPIOParameters=GPIO_Speed
PH10.GPIO_Speed=GPIO_SPEED_FREQ_VERY_HIGH
PH10.Mode=RGB888
PH10.Signal=LTDC_R4
PH11.GPIOParameters=GPIO_Speed
PH11.GPIO_Speed=GPIO_SPEED_FREQ_VERY_HIGH
PH11.Mode=RGB888
PH11.Signal=LTDC_R5
PH12.GPIOParameters=PinState
PH12.PinState=GPIO_PIN_SET
PH12.Signal=GPIO_Output
PH14.Mode=Asynchronous
PH14.Signal=UART4_RX
PH15.Mode=RGB888
PH15.Signal=LTDC_G4
PH2.Mode=RGB888
PH2.Signal=LTDC_R0
PH3.GPIOParameters=GPIO_Speed
PH3.GPIO_Speed=GPIO_SPEED_FREQ_VERY_HIGH
PH3.Mode=RGB888
PH3.Signal=LTDC_R1
PH4.GPIOParameters=GPIO_Speed
PH4.GPIO_Speed=GPIO_SPEED_FREQ_VERY_HIGH
PH4.Mode=RGB888
PH4.Signal=LTDC_G5
PH7.Mode=I2C
PH7.Signal=I2C3_SCL
PH8.GPIOParameters=GPIO_Speed
PH8.GPIO_Speed=GPIO_SPEED_FREQ_VERY_HIGH
PH8.Mode=RGB888
PH8.Signal=LTDC_R2
PH9.GPIOParameters=GPIO_Speed
PH9.GPIO_Speed=GPIO_SPEED_FREQ_VERY_HIGH
PH9.Mode=RGB888
PH9.Signal=LTDC_R3
RCC.SYSCLKFreq_VALUE=550000000
RCC.SYSCLKSource=RCC_SYSCLKSOURCE_PLLCLK
board=custom

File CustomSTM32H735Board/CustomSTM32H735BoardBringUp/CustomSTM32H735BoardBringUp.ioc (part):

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Mcu.Name=STM32H735IGTx
Mcu.Package=LQFP176
Mcu.UserName=STM32H735IGTx
PA0.Mode=Asynchronous
PA0.Signal=UART4_TX
PA1.Mode=RGB888
PA1.Signal=LTDC_R2
PA10.Mode=RGB888
PA10.Signal=LTDC_B1
PA11.Mode=RGB888
PA11.Signal=LTDC_R4
PA13(JTMS/SWDIO).Mode=Serial_Wire
PA13(JTMS/SWDIO).Signal=DEBUG_JTMS-SWDIO
PA14(JTCK/SWCLK).Mode=Serial_Wire
PA14(JTCK/SWCLK).Signal=DEBUG_JTCK-SWCLK
PA2.Mode=RGB888
PA2.Signal=LTDC_R1
PA3.Mode=RGB888
PA3.Signal=LTDC_B5
PA4.Signal=COMP_DAC11_group
PA5.Signal=COMP_DAC12_group
PA6.Mode=OCTOSPI1_IOL_Port1L
PA6.Signal=OCTOSPIM_P1_IO3
PA7.Mode=RGB888
PA7.Signal=LTDC_VSYNC
PA8.Mode=RGB888
PA8.Signal=LTDC_B3
PA9.Mode=RGB888
PA9.Signal=LTDC_R5
PB0.Mode=RGB888
PB0.Signal=LTDC_R3
PB1.Mode=RGB888
PB1.Signal=LTDC_R6
PB10.Mode=I2C
PB10.Signal=I2C2_SCL
PB11.Mode=I2C
PB11.Signal=I2C2_SDA
PB15.Mode=RGB888
PB15.Signal=LTDC_G7
PB2.Mode=O1_P1_CLK
PB2.Signal=OCTOSPIM_P1_CLK
PB6.Mode=I2C
PB6.Signal=I2C1_SCL
PB7.Mode=I2C
PB7.Signal=I2C1_SDA
PB8.Mode=RGB888
PB8.Signal=LTDC_B6
PC0.Mode=RGB888
PC0.Signal=LTDC_G2
PC1.Mode=RGB888
PC1.Signal=LTDC_G5
PC11.Mode=Asynchronous
PC11.Signal=UART4_RX
PC2_C.Mode=IN0-Single-Ended
PC2_C.Signal=ADC3_INP0
PC3_C.Mode=OCTOSPI1_IOH_Port1H
PC3_C.Signal=OCTOSPIM_P1_IO6
PC4.Mode=RGB888
PC4.Signal=LTDC_R7
PC5.Mode=OCTOSPI1_Port1_DQS
PC5.Signal=OCTOSPIM_P1_DQS
PC6.Mode=RGB888
PC6.Signal=LTDC_HSYNC
PC9.Mode=RGB888
PC9.Signal=LTDC_B2
PD0.Signal=GPIO_Output
PD10.Signal=GPIO_Output
PD2.Mode=RGB888
PD2.Signal=LTDC_B7
PE10.Mode=OCTOSPI1_IOH_Port1H
PE10.Signal=OCTOSPIM_P1_IO7
PE11.Mode=RGB888
PE11.Signal=LTDC_G3
PE12.Mode=RGB888
PE12.Signal=LTDC_B4
PE14.Mode=RGB888
PE14.Signal=LTDC_CLK
PE2.Mode=OCTOSPI1_IOL_Port1L
PE2.Signal=OCTOSPIM_P1_IO2
PE4.Mode=RGB888
PE4.Signal=LTDC_B0
PE5.Mode=RGB888
PE5.Signal=LTDC_G0
PE6.Mode=RGB888
PE6.Signal=LTDC_G1
PE7.Mode=OCTOSPI1_IOH_Port1H
PE7.Signal=OCTOSPIM_P1_IO4
PE8.Mode=OCTOSPI1_IOH_Port1H
PE8.Signal=OCTOSPIM_P1_IO5
PF0.Mode=OCTOSPI2_IOL_Port2L
PF0.Signal=OCTOSPIM_P2_IO0
PF1.Mode=OCTOSPI2_IOL_Port2L
PF1.Signal=OCTOSPIM_P2_IO1
PF10.Mode=RGB888
PF10.Signal=LTDC_DE
PF11.Mode=IN2-Single-Ended
PF11.Signal=ADC1_INP2
PF12.Mode=OCTOSPI2_Port2_DQS
PF12.Signal=OCTOSPIM_P2_DQS
PF13.Mode=IN2-Single-Ended
PF13.Signal=ADC2_INP2
PF2.Mode=OCTOSPI2_IOL_Port2L
PF2.Signal=OCTOSPIM_P2_IO2
PF3.Mode=OCTOSPI2_IOL_Port2L
PF3.Signal=OCTOSPIM_P2_IO3
PF4.Mode=O2_P2_CLK
PF4.Signal=OCTOSPIM_P2_CLK
PF6.Mode=Encoder_Interface
PF6.Signal=TIM23_CH1
PF7.Signal=S_TIM23_CH2
PF8.Mode=OCTOSPI1_IOL_Port1L
PF8.Signal=OCTOSPIM_P1_IO0
PF9.Mode=OCTOSPI1_IOL_Port1L
PF9.Signal=OCTOSPIM_P1_IO1
PG0.Mode=OCTOSPI2_IOH_Port2H
PG0.Signal=OCTOSPIM_P2_IO4
PG1.Mode=OCTOSPI2_IOH_Port2H
PG1.Signal=OCTOSPIM_P2_IO5
PG10.Mode=OCTOSPI2_IOH_Port2H
PG10.Signal=OCTOSPIM_P2_IO6
PG11.Mode=OCTOSPI2_IOH_Port2H
PG11.Signal=OCTOSPIM_P2_IO7
PG12.Mode=OCTOSPI2_Port2_NCS
PG12.Signal=OCTOSPIM_P2_NCS
PG13.Mode=RGB888
PG13.Signal=LTDC_R0
PG15.Signal=GPIO_Output
PG6.Mode=OCTOSPI1_Port1_NCS
PG6.Signal=OCTOSPIM_P1_NCS
PH0-OSC_IN.Mode=HSE-External-Oscillator
PH0-OSC_IN.Signal=RCC_OSC_IN
PH1-OSC_OUT.Mode=HSE-External-Oscillator
PH1-OSC_OUT.Signal=RCC_OSC_OUT
PJ11.Mode=RGB888
PJ11.Signal=LTDC_G4
PK1.Mode=RGB888
PK1.Signal=LTDC_G6
RCC.SYSCLKFreq_VALUE=550000000
RCC.SYSCLKSource=RCC_SYSCLKSOURCE_PLLCLK
board=custom
